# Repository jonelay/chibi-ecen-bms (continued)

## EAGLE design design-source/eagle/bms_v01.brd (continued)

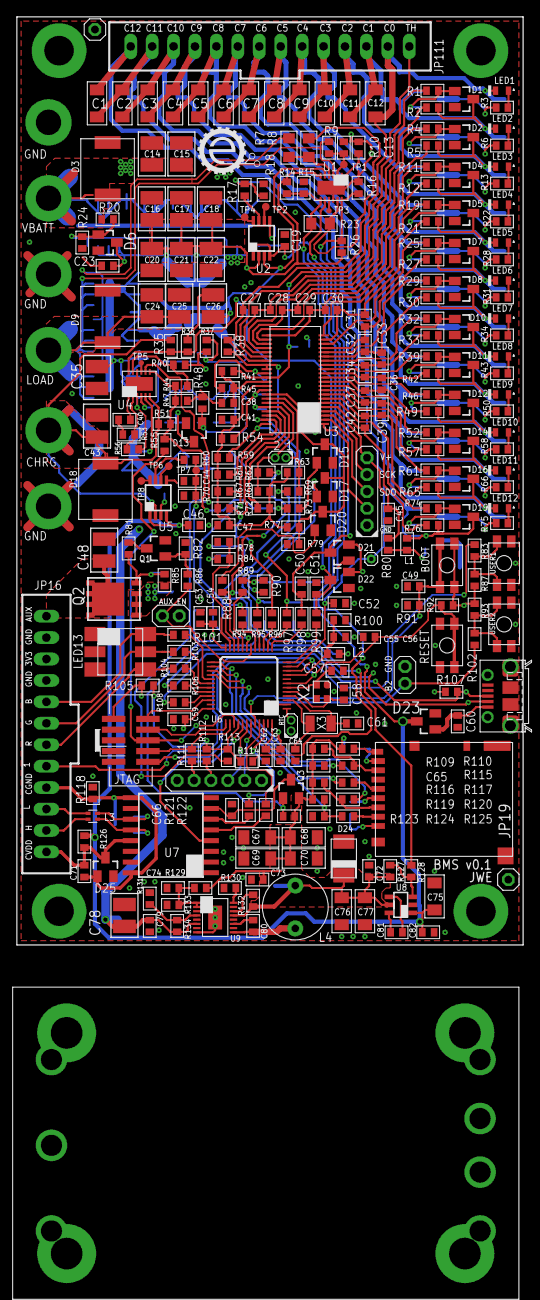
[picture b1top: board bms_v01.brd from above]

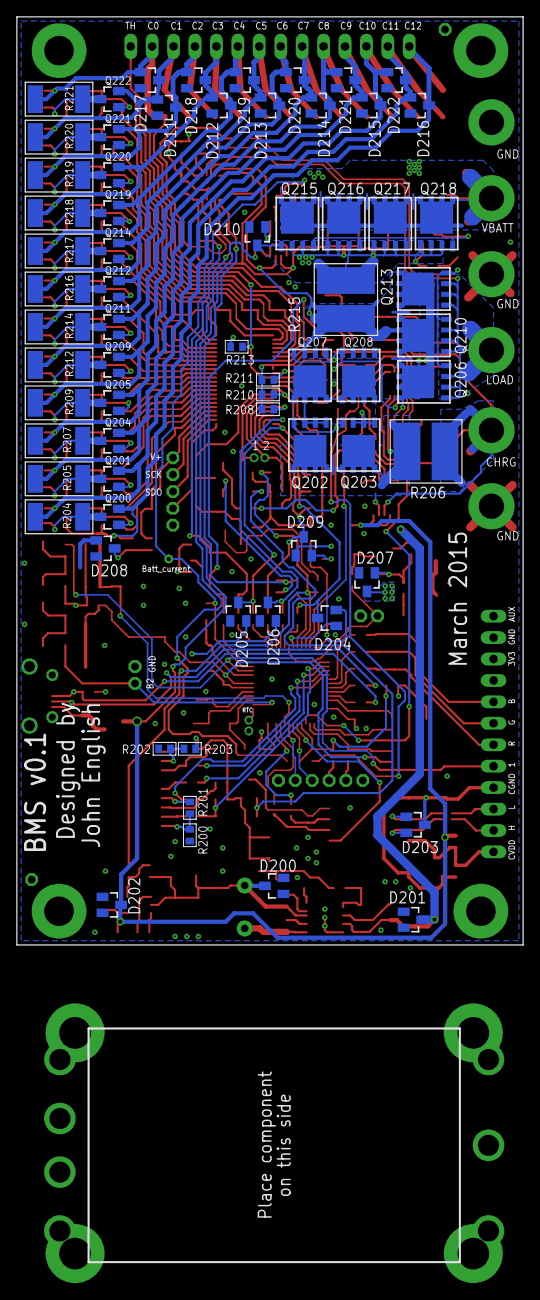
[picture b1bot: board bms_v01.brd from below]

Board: 4 copper layers, 60.0 x 110.0 mm, 379 parts (68 on the bottom side), 211 nets.

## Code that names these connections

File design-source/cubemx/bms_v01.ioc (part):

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Mcu.Name=STM32F303C(B-C)Tx
Mcu.Package=LQFP48
Mcu.UserName=STM32F303CCTx
PA0.GPIOParameters=GPIO_Label
PA0.GPIO_Label=Button 1
PA0.Mode=Wake-Up-1
PA0.Signal=SYS_WKUP1
PA1.GPIOParameters=GPIO_Label
PA1.GPIO_Label=Battery Current
PA1.Mode=INP
PA1.Signal=COMP1_INP
PA10.GPIOParameters=GPIO_Label
PA10.GPIO_Label=LED_R
PA10.Signal=GPIO_Output
PA11.Mode=Device
PA11.Signal=USB_DM
PA12.Mode=Device
PA12.Signal=USB_DP
PA13.Mode=JTAG(5-pin)
PA13.Signal=SYS_JTMS-SWDIO
PA14.Mode=JTAG(5-pin)
PA14.Signal=SYS_JTCK-SWCLK
PA15.GPIOParameters=GPIO_Label
PA15.GPIO_Label=Interlock
PA15.Mode=JTAG(5-pin)
PA15.Signal=SYS_JTDI
PA2.GPIOParameters=GPIO_Label
PA2.GPIO_Label=Chage Current
PA2.Mode=IN3-Single-Ended
PA2.Signal=ADC1_IN3
PA3.GPIOParameters=GPIO_Label
PA3.GPIO_Label=Battery Voltage
PA3.Mode=INP
PA3.Signal=COMP2_INP
PA4.Mode=NSS_Signal_Hard
PA4.Signal=SPI1_NSS
PA5.Mode=Full_Duplex_Master
PA5.Signal=SPI1_SCK
PA6.Mode=Full_Duplex_Master
PA6.Signal=SPI1_MISO
PA7.Mode=Full_Duplex_Master
PA7.Signal=SPI1_MOSI
PA8.GPIOParameters=GPIO_Label
PA8.GPIO_Label=LED_B
PA8.Signal=GPIO_Output
PA9.GPIOParameters=GPIO_Label
PA9.GPIO_Label=LED_G
PA9.Signal=GPIO_Output
PB0.GPIOParameters=GPIO_Label
PB0.GPIO_Label=Discharge Voltage
PB0.Mode=INP
PB0.Signal=COMP4_INP
PB1.GPIOParameters=GPIO_Label
PB1.GPIO_Label=Charge Enable
PB1.Signal=GPIO_Output
PB10.GPIOParameters=GPIO_Label
PB10.GPIO_Label=3V3 Power good
PB10.Signal=GPIO_Input
PB11.GPIOParameters=GPIO_Label
PB11.GPIO_Label=Discharge voltage
PB11.Mode=INP
PB11.Signal=COMP6_INP
PB12.Mode=NSS_Signal_Hard
PB12.Signal=SPI2_NSS
PB13.Mode=Full_Duplex_Master
PB13.Signal=SPI2_SCK
PB14.Mode=Full_Duplex_Master
PB14.Signal=SPI2_MISO
PB15.Mode=Full_Duplex_Master
PB15.Signal=SPI2_MOSI
PB2.GPIOParameters=GPIO_Label
PB2.GPIO_Label=Discharge Enable
PB2.Signal=GPIO_Output
PB3.Mode=JTAG(5-pin)
PB3.Signal=SYS_JTDO-TRACESWO
PB4.GPIOParameters=GPIO_Label
PB4.GPIO_Label=Fault
PB4.Mode=JTAG(5-pin)
PB4.Signal=SYS_NJTRST
PB5.GPIOParameters=GPIO_Label
PB5.GPIO_Label=CAN_PWR
PB5.Signal=GPIO_Input
PB6.Mode=Asynchronous
PB6.Signal=USART1_TX
PB7.Mode=Asynchronous
PB7.Signal=USART1_RX
PB8.Mode=Master
PB8.Signal=CAN_RX
PB9.Mode=Master
PB9.Signal=CAN_TX
PC13.GPIOParameters=GPIO_Label
PC13.GPIO_Label=Button 2
PC13.Mode=WakeUp
PC13.Signal=RTC_OUT_ALARM
PC14-OSC32_IN.Mode=LSE-External-Oscillator
PC14-OSC32_IN.Signal=RCC_OSC32_IN
PC15-OSC32_OUT.Mode=LSE-External-Oscillator
PC15-OSC32_OUT.Signal=RCC_OSC32_OUT
PF0-OSC_IN.Mode=HSE-External-Oscillator
PF0-OSC_IN.Signal=RCC_OSC_IN
PF1-OSC_OUT.Mode=HSE-External-Oscillator
PF1-OSC_OUT.Signal=RCC_OSC_OUT
RCC.HSEPLLFreq_Value=8000000
RCC.HSEState-ClockTree=RCC_HSE_ON
RCC.HSE_VALUE=8000000
RCC.SYSCLKFreq_VALUE=8000000

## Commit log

2026-01-08 Reorganized Spring 2015 BMS project for initial open-source hardware release.
2026-01-08 Add PCB photos to README
2026-01-08 Update README.md
    Add status flags to the top of readme.md
2026-01-08 Update README.md
    Made readme format more consistent with chibi-ecen-bldc sister project
2026-01-08 Update README.md
    Fixed date in readme text
